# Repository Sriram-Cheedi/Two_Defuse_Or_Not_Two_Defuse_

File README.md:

# Two Defuse or Not Two Defuse
> **Created by The Barbies** | COMS30043 2025 Team Project

This project aims to create an innovative and tense cooperative experience for players by utilising custom hardware. 

The application runs on an asymmetric two-input system: one player operates within the Unity game world created for the project, while the other operates a custom physical hardware controller to communicate and defuse the bomb.

Technical report on the project can be found [here](./docs/Report_Redacted.pdf) (May require downloading due to file size).

Watch the technical video and trailer [here](https://www.youtube.com/watch?v=A18D9NIgztE).

---

## Project Setup

To fully experience this project, a physical 'hardware bomb' controller is required.

### Prerequisites
*   **Microcontroller:** Teensy 4.1
*   **IDE:** Visual Studio Code with the [PlatformIO extension](https://platformio.org/)
*   **Game Engine:** Unity 6.3 LTS

### 1. Hardware Setup
1. Clone this git repository to your local machine.
2. Open the `Hardware/ControllerV0.1` folder in Visual Studio Code.
3. Ensure the **PlatformIO** extension is installed and active.
4. Plug the Teensy 4.1 microcontroller into your PC via USB.
5. Press the PlatformIO **Upload** button (the right-pointing arrow in the bottom status bar) and wait for the upload to finish.

### 2. Software (Unity) Setup
1. Open the `Team_Project` folder in the Unity Editor and import any required packages.
2. Build the project using **Build Profiles**, selecting your target operating system.
3. Connect the flashed hardware controller to any open serial USB port on your device.
4. Launch the built executable.
5. Enjoy and try not to explode!

> **Note:** If you do not have the required custom hardware, the level will still open and assign a Mock API. However, the game will **not be playable**, as the physical interactions required to navigate and access the game states will be absent.

---

## Project Structure

```text
├── Games Project Pitch Design Documents.pdf
├── Hardware
│   ├── Circuit_Designs
│   ├── ControllerV0.1
│   ├── Example Code
│   └── Manufacturing Drawings
├── Hardware-Software_Interaction.md
├── README.md
├── Team_Project  (Unity Project Root)
│   ├── Assets
│   ├── Packages
│   ├── ProjectSettings
│   └── ... (Builds and project files)
└── The Barbies - Team Project Pitches.pdf

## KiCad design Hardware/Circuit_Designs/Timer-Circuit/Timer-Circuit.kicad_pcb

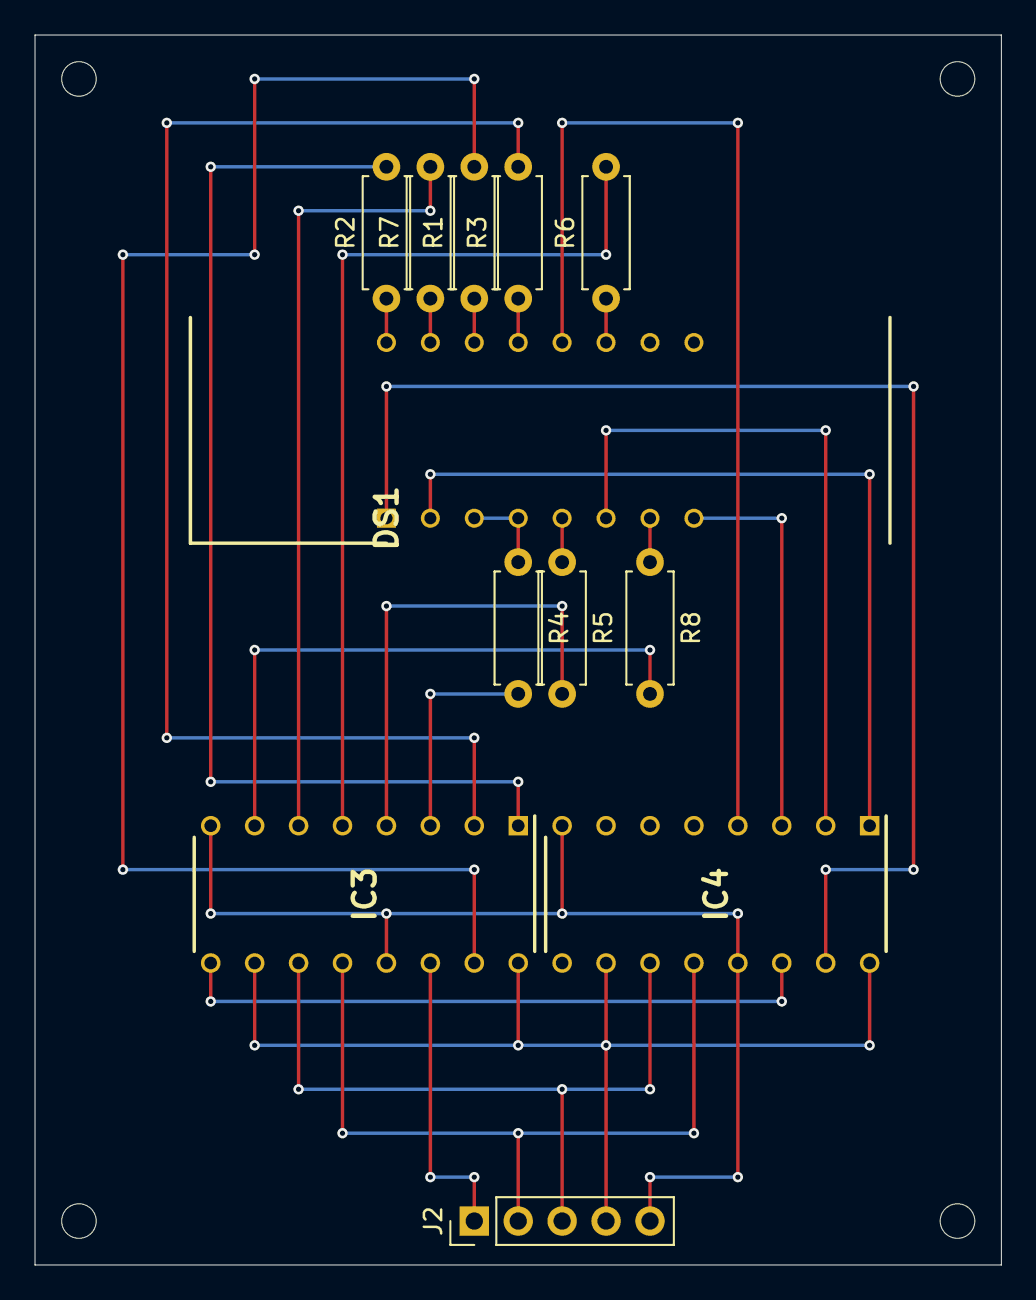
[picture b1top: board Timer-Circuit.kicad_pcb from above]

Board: 2 copper layers, 55.9 x 71.1 mm, 12 parts (0 on the bottom side), 27 nets.

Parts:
DS1: TDCR1060M; DIPS1016W50P254L4020H725Q16N
IC3, IC4: SN74HC595NE4; DIP794W53P254L1930H508Q16N
J2: Conn_01x05; PinHeader_1x05_P2.54mm_Vertical
R1, R2, R3, R4, R5, R6, R7, R8: R_Small; R_Axial_DIN0207_L6.3mm_D2.5mm_P7.62mm_Horizontal

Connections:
unnamed: DS1.14 (ANODE_A), R1.1
unnamed: DS1.16 (ANODE_B), R2.1
unnamed: DS1.13 (ANODE_C), R3.1
unnamed: DS1.3 (ANODE_D), DS1.4 (COMMON_CATHODE_L1_L2), R4.1
unnamed: DS1.7 (ANODE_DP), R8.1
unnamed: DS1.5 (ANODE_E), R5.1
unnamed: DS1.11 (ANODE_F), R6.1
unnamed: DS1.15 (ANODE_G), R7.1
unnamed: DS1.12 (ANODE_L1L2), IC4.4 (QE)
unnamed: DS1.1 (COMMON_CATHODE_D1), IC4.15 (QA)
unnamed: DS1.2 (COMMON_CATHODE_D2), IC4.1 (QB)
unnamed: DS1.6 (COMMON_CATHODE_D3), IC4.2 (QC)
unnamed: DS1.8 (COMMON_CATHODE_D4), IC4.3 (QD)
unnamed: IC3.8 (GND), IC3.13 (~OE), IC4.8 (GND), IC4.13 (~OE), J2.5
unnamed: IC3.15 (QA), R1.2
unnamed: IC3.1 (QB), R2.2
unnamed: IC3.2 (QC), R3.2
unnamed: IC3.3 (QD), R4.2
unnamed: IC3.4 (QE), R5.2
unnamed: IC3.5 (QF), R6.2
unnamed: IC3.6 (QG), R7.2
unnamed: IC3.9 (QH'), IC4.14 (SER)
unnamed: IC3.7 (QH), R8.2
unnamed: IC3.12 (RCLK), IC4.12 (RCLK), J2.2
unnamed: IC3.14 (SER), J2.1
unnamed: IC3.11 (SRCLK), IC4.11 (SRCLK), J2.3
unnamed: IC3.10 (~SRCLR), IC3.16 (VCC), IC4.10 (~SRCLR), IC4.16 (VCC), J2.4

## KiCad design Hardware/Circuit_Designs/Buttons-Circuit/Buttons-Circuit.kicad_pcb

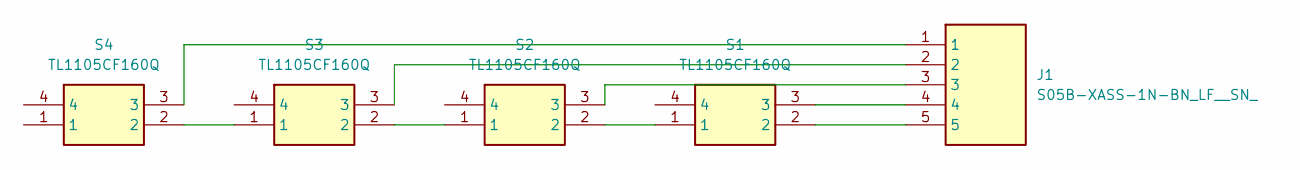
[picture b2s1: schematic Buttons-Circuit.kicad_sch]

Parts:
J1: S05B-XASS-1N-BN_LF__SN_; S05BXASS1NBNLFSN; Manufacturer_Part_Number S05B-XASS-1N-BN(LF)(SN); Mouser Part Number 306-S05BXASS1NBNLFSN
S1, S2, S3, S4: TL1105CF160Q; Manufacturer_Part_Number TL1105CF160Q; Mouser Part Number 612-TL1105C

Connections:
unnamed: J1.1, S4.3
unnamed: J1.2, S3.3
unnamed: J1.3, S2.3
unnamed: J1.4, S1.3
unnamed: J1.5, S1.2
unnamed: S1.1, S2.2
unnamed: S2.1, S3.2
unnamed: S3.1, S4.2

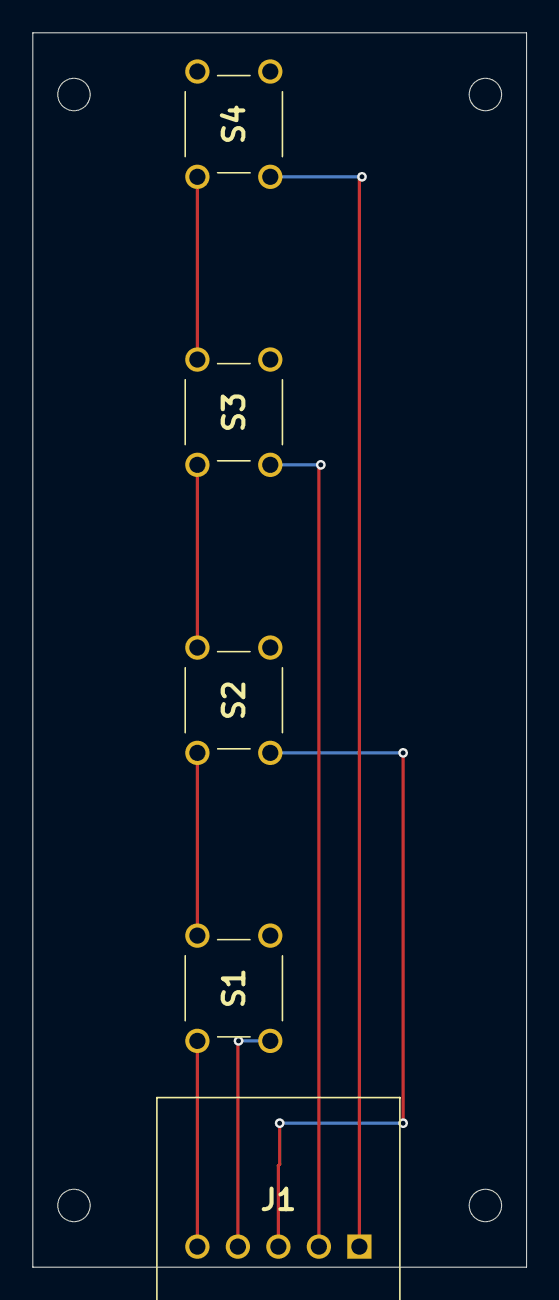
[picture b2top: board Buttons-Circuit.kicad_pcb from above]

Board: 2 copper layers, 30.5 x 76.2 mm, 5 parts (0 on the bottom side), 8 nets.

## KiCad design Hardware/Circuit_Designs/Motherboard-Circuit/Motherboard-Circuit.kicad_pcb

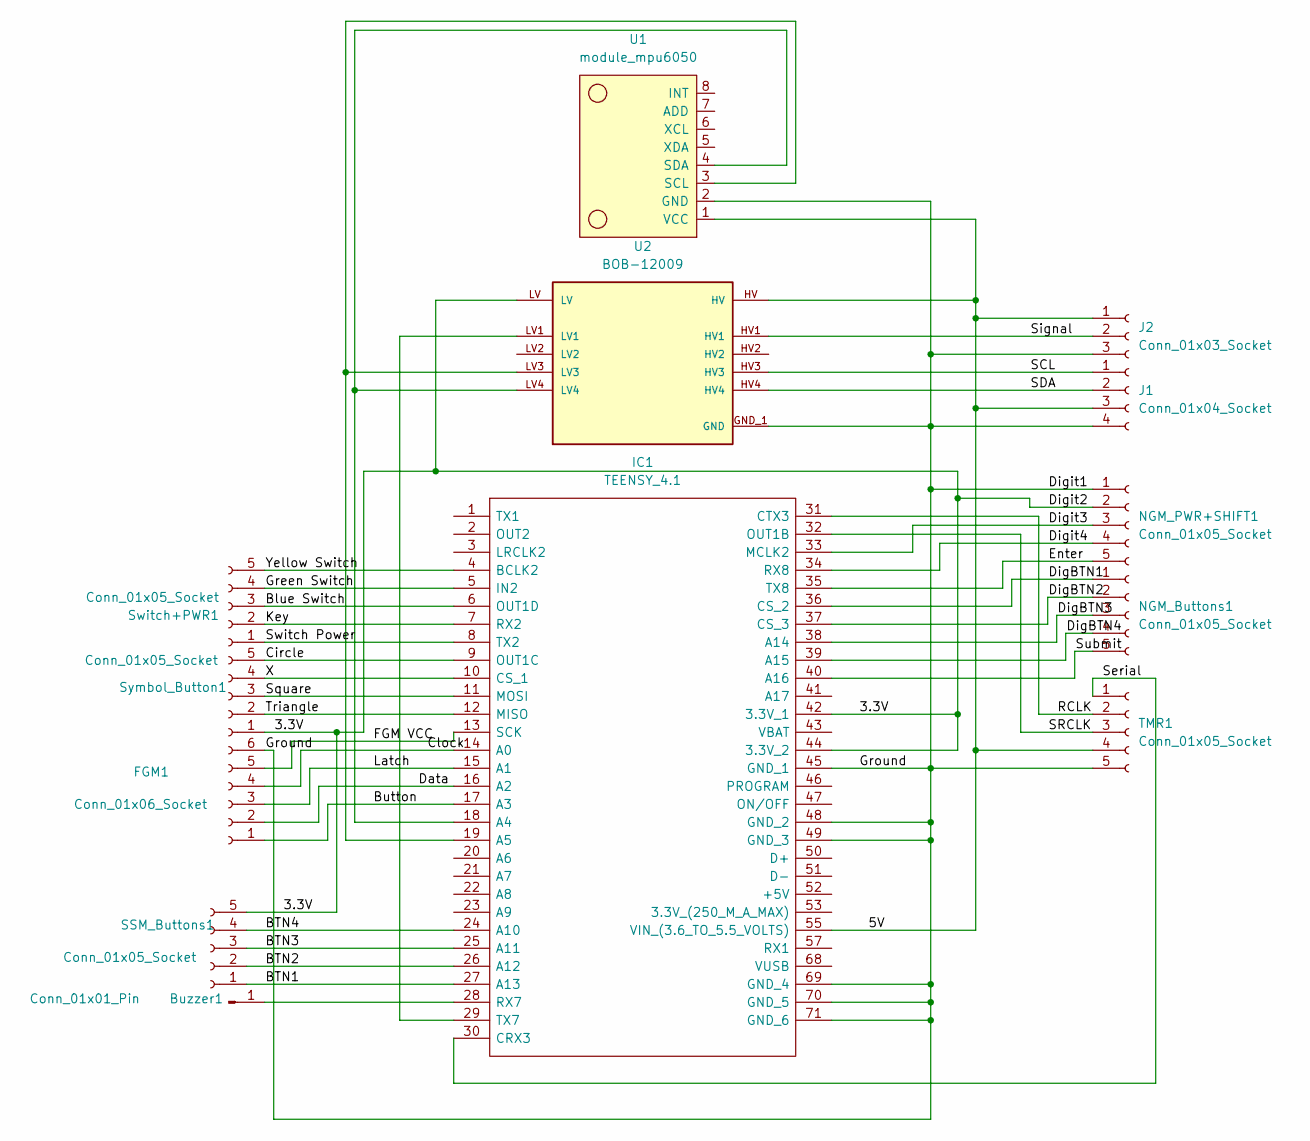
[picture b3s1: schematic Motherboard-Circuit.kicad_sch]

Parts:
Buzzer1: Conn_01x01_Pin; PinHeader_1x01_P2.54mm_Vertical
FGM1: Conn_01x06_Socket; Molex_KK-254_AE-6410-06A_1x06_P2.54mm_Vertical
IC1: TEENSY_4.1; TEENSY41; Manufacturer_Part_Number TEENSY 4.1
J1: Conn_01x04_Socket; Molex_KK-254_AE-6410-04A_1x04_P2.54mm_Vertical
J2: Conn_01x03_Socket; Molex_KK-254_AE-6410-03A_1x03_P2.54mm_Vertical
NGM_Buttons1: Conn_01x05_Socket; Molex_KK-254_AE-6410-05A_1x05_P2.54mm_Vertical
NGM_PWR+SHIFT1: Conn_01x05_Socket; Molex_KK-254_AE-6410-05A_1x05_P2.54mm_Vertical
SSM_Buttons1: Conn_01x05_Socket; Molex_KK-254_AE-6410-05A_1x05_P2.54mm_Vertical
Switch+PWR1: Conn_01x05_Socket; Molex_KK-254_AE-6410-05A_1x05_P2.54mm_Vertical
Symbol_Button1: Conn_01x05_Socket; Molex_KK-254_AE-6410-05A_1x05_P2.54mm_Vertical
TMR1: Conn_01x05_Socket; Molex_KK-254_AE-6410-05A_1x05_P2.54mm_Vertical
U1: module_mpu6050
U2: BOB-12009; CONV_BOB-12009; PARTREV 01

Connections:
/3.3V: IC1.42 (3.3V_1), IC1.44 (3.3V_2), NGM_PWR+SHIFT1.2, SSM_Buttons1.5, Symbol_Button1.1, U2.LV
/5V: IC1.55 (VIN_(3.6_TO_5.5_VOLTS)), J1.3, J2.1, TMR1.4, U1.1 (VCC), U2.HV
/BTN1: IC1.27 (A13), SSM_Buttons1.1
/BTN2: IC1.26 (A12), SSM_Buttons1.2
/BTN3: IC1.25 (A11), SSM_Buttons1.3
/BTN4: IC1.24 (A10), SSM_Buttons1.4
/Blue Switch: IC1.6 (OUT1D), Switch+PWR1.3
/Button: FGM1.1, IC1.17 (A3)
/Circle: IC1.9 (OUT1C), Symbol_Button1.5
/Clock: FGM1.4, IC1.14 (A0)
/Clock_Pin: IC1.35 (TX8), NGM_PWR+SHIFT1.5
/DS_Pin: IC1.33 (MCLK2), NGM_PWR+SHIFT1.3
/Data: FGM1.2, IC1.16 (A2)
/DigBTN1: IC1.36 (CS_2), NGM_Buttons1.1
/DigBTN2: IC1.37 (CS_3), NGM_Buttons1.2
/DigBTN3: IC1.38 (A14), NGM_Buttons1.3
/DigBTN4: IC1.39 (A15), NGM_Buttons1.4
/FGM VCC: FGM1.5, IC1.13 (SCK)
/Green Switch: IC1.5 (IN2), Switch+PWR1.4
/Key: IC1.7 (RX2), Switch+PWR1.2
/Latch: FGM1.3, IC1.15 (A1)
/Latch Pin: IC1.34 (RX8), NGM_PWR+SHIFT1.4
/RCLK: IC1.31 (CTX3), TMR1.2
/SCL: J1.1, U2.HV3
/SDA: J1.2, U2.HV4
/SRCLK: IC1.32 (OUT1B), TMR1.3
/Serial: IC1.30 (CRX3), TMR1.1
/Signal: J2.2, U2.HV1
/Square: IC1.11 (MOSI), Symbol_Button1.3
/Submit: IC1.40 (A16), NGM_Buttons1.5
/Triangle: IC1.12 (MISO), Symbol_Button1.2
/X: IC1.10 (CS_1), Symbol_Button1.4
/Yellow Switch: IC1.4 (BCLK2), Switch+PWR1.5
GND: FGM1.6, IC1.45 (GND_1), IC1.48 (GND_2), IC1.49 (GND_3), IC1.69 (GND_4), IC1.70 (GND_5), IC1.71 (GND_6), J1.4, J2.3, NGM_PWR+SHIFT1.1, TMR1.5, U1.2 (GND), U2.GND_1 (GND), U2.GND_2 (GND)
unnamed: Buzzer1.1, IC1.28 (RX7)
unnamed: IC1.18 (A4), U1.4 (SDA), U2.LV4
unnamed: IC1.19 (A5), U1.3 (SCL), U2.LV3
unnamed: IC1.8 (TX2), Switch+PWR1.1
unnamed: IC1.29 (TX7), U2.LV1

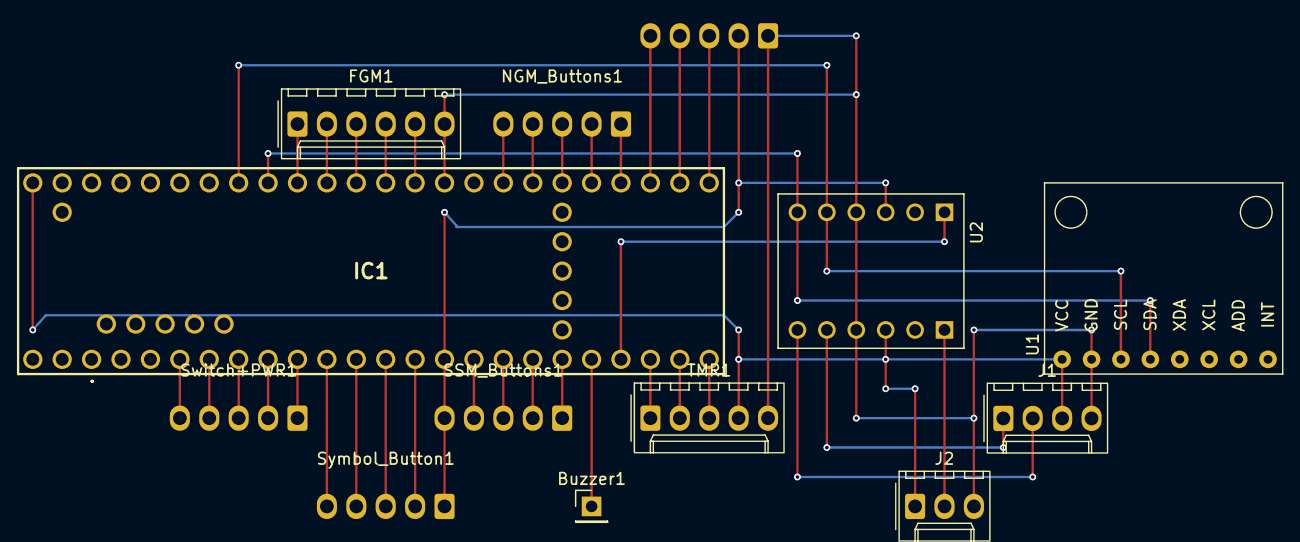
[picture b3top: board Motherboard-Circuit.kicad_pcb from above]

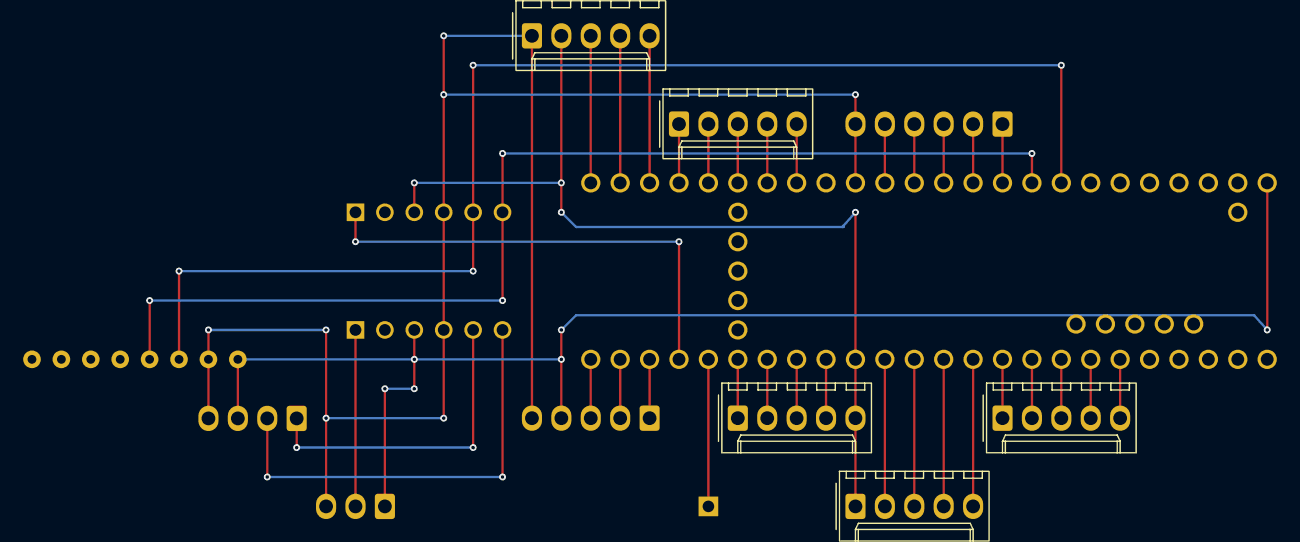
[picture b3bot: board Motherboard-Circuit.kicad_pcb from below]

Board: 2 copper layers, 13 parts (5 on the bottom side), 39 nets.

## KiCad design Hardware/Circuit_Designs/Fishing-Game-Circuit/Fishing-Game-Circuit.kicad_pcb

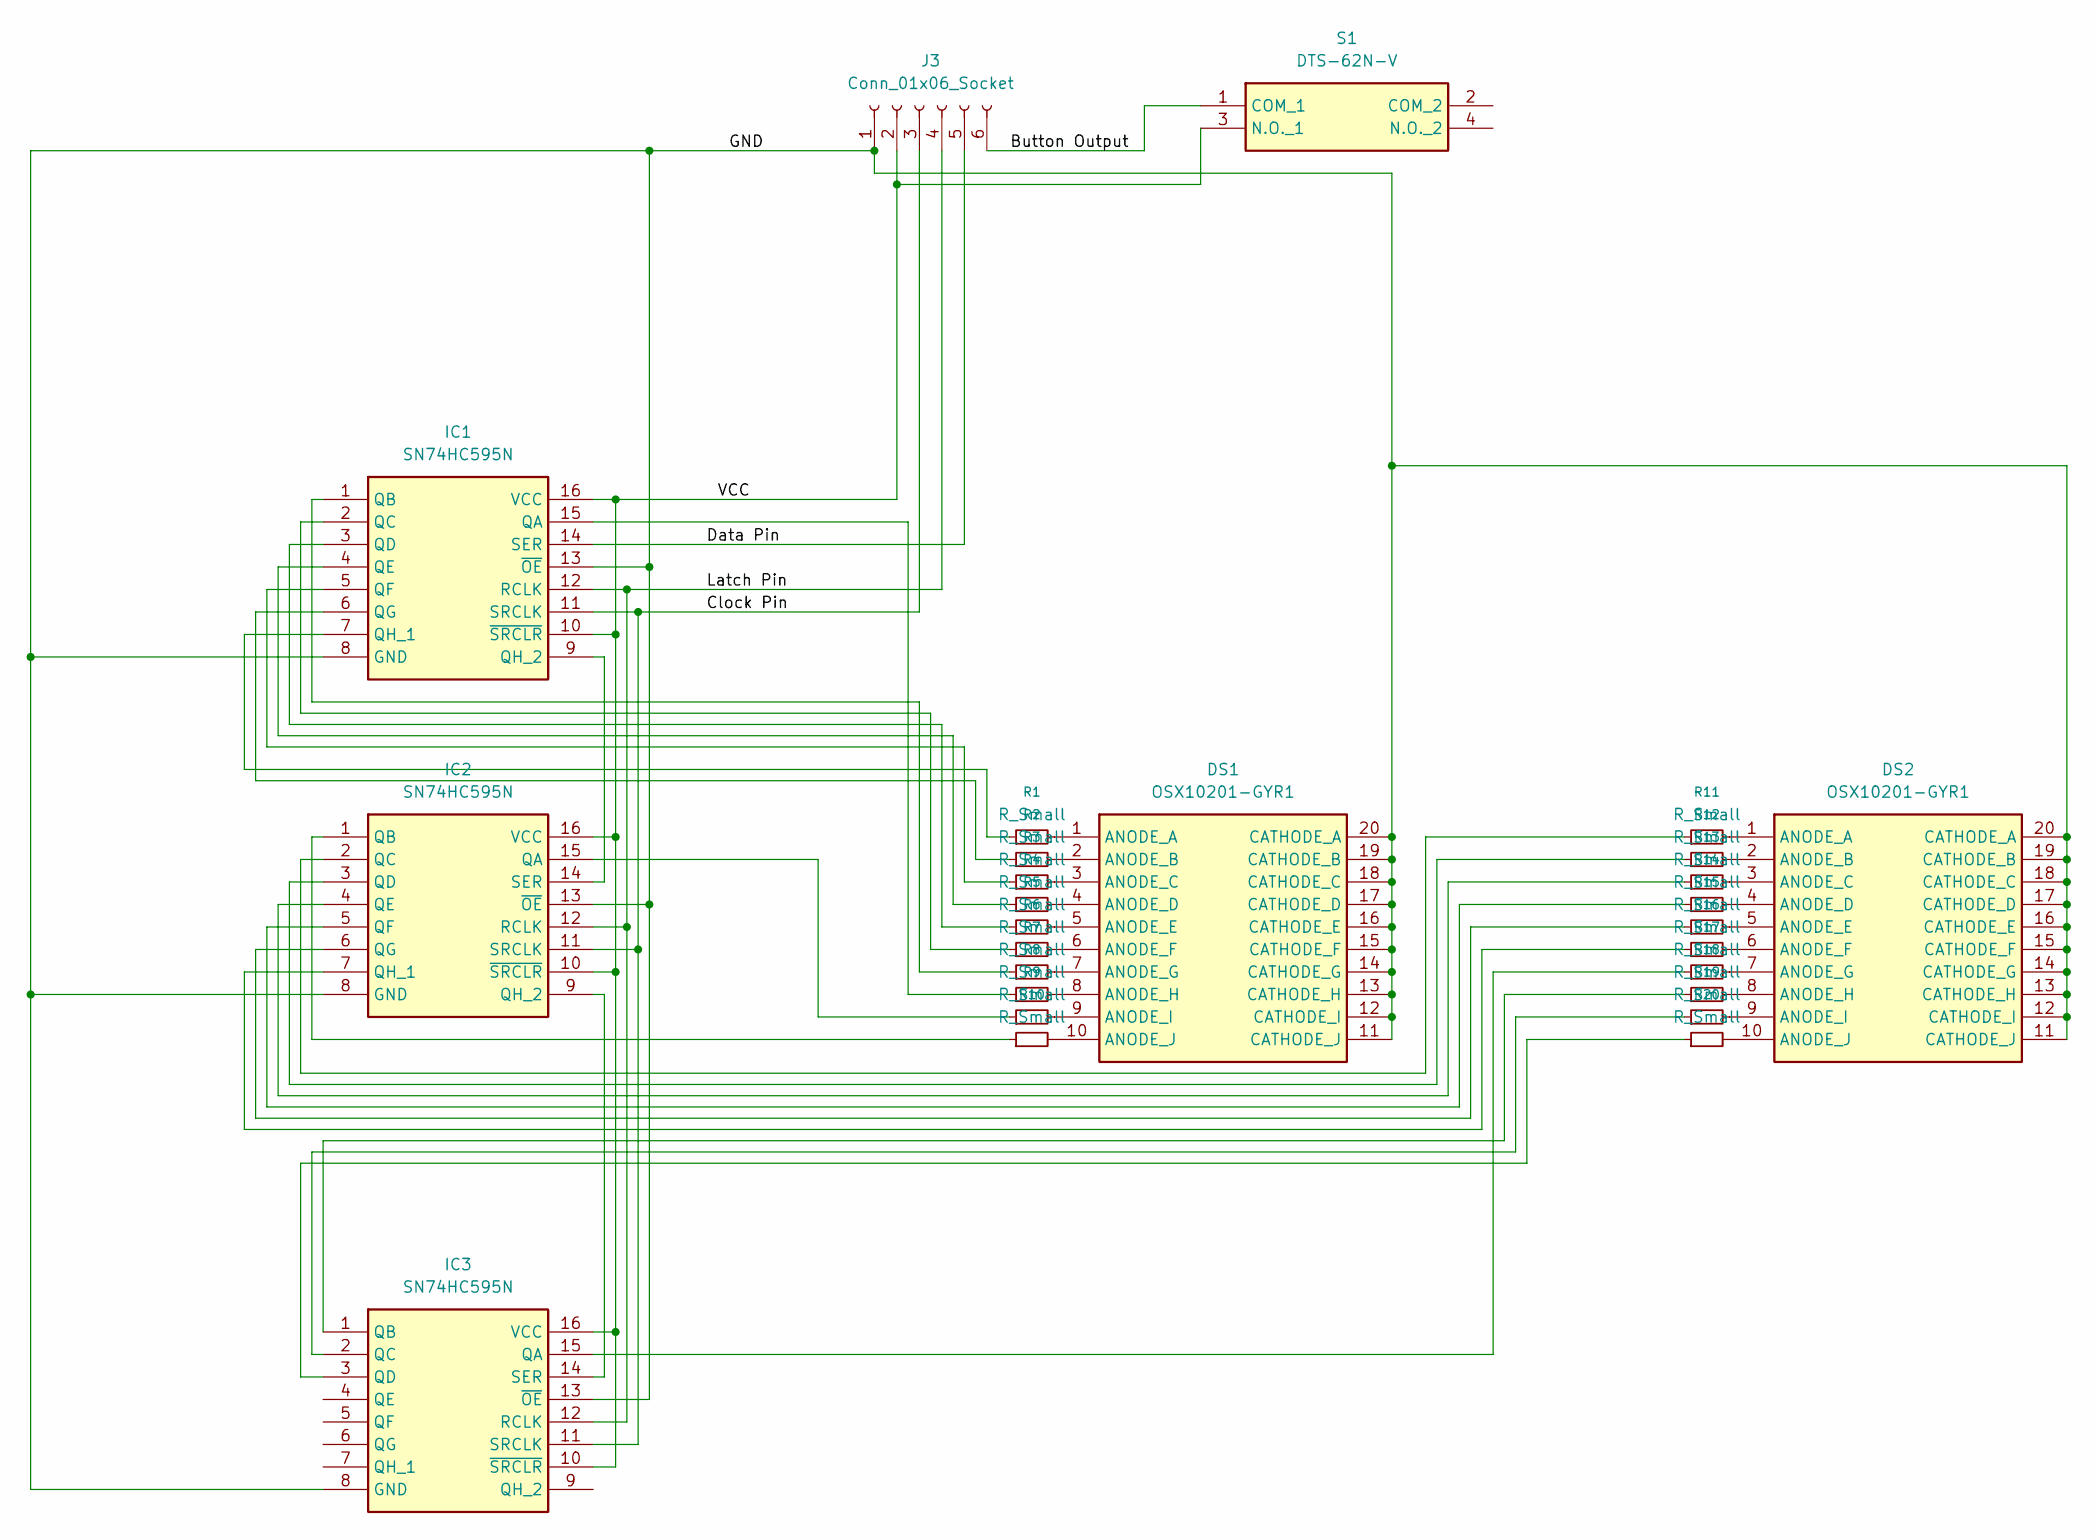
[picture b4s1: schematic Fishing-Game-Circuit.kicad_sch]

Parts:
DS1, DS2: OSX10201-GYR1; DIPS760W45P254L2550H815Q20N; Manufacturer_Part_Number OSX10201-GYR1
IC1, IC2, IC3: SN74HC595N; DIP794W53P254L1930H508Q16N; Manufacturer_Part_Number SN74HC595N; Mouser Part Number 595-SN74HC595N
J3: Conn_01x06_Socket; Molex_SL_171971-0006_1x06_P2.54mm_Vertical
R1, R2, R3, R4, R5, R6, R7, R8, R9, R10, R11, R12, R13, R14, R15, R16, R17, R18, R19, R20: R_Small; R_Axial_DIN0207_L6.3mm_D2.5mm_P7.62mm_Horizontal
S1: DTS-62N-V; DTS62NV; Manufacturer_Part_Number DTS-62N-V; Mouser Part Number 113-DTS-62N-V

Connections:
/Button Output: J3.6, S1.1 (COM_1)
/Clock Pin: IC1.11 (SRCLK), IC2.11 (SRCLK), IC3.11 (SRCLK), J3.3
/Data Pin: IC1.14 (SER), J3.5
/GND: DS1.11 (CATHODE_J), DS1.12 (CATHODE_I), DS1.13 (CATHODE_H), DS1.14 (CATHODE_G), DS1.15 (CATHODE_F), DS1.16 (CATHODE_E), DS1.17 (CATHODE_D), DS1.18 (CATHODE_C), DS1.19 (CATHODE_B), DS1.20 (CATHODE_A), DS2.11 (CATHODE_J), DS2.12 (CATHODE_I), DS2.13 (CATHODE_H), DS2.14 (CATHODE_G), DS2.15 (CATHODE_F), DS2.16 (CATHODE_E), DS2.17 (CATHODE_D), DS2.18 (CATHODE_C), DS2.19 (CATHODE_B), DS2.20 (CATHODE_A), IC1.8 (GND), IC1.13 (~OE), IC2.8 (GND), IC2.13 (~OE), IC3.8 (GND), IC3.13 (~OE), J3.1
/Latch Pin: IC1.12 (RCLK), IC2.12 (RCLK), IC3.12 (RCLK), J3.4
/VCC: IC1.10 (~SRCLR), IC1.16 (VCC), IC2.10 (~SRCLR), IC2.16 (VCC), IC3.10 (~SRCLR), IC3.16 (VCC), J3.2, S1.3 (N.O._1)
unnamed: DS1.1 (ANODE_A), R1.2
unnamed: DS1.2 (ANODE_B), R2.2
unnamed: DS1.3 (ANODE_C), R3.2
unnamed: DS1.4 (ANODE_D), R4.2
unnamed: DS1.5 (ANODE_E), R5.2
unnamed: DS1.6 (ANODE_F), R6.2
unnamed: DS1.7 (ANODE_G), R7.2
unnamed: DS1.8 (ANODE_H), R8.2
unnamed: DS1.9 (ANODE_I), R9.2
unnamed: DS1.10 (ANODE_J), R10.2
unnamed: DS2.1 (ANODE_A), R11.2
unnamed: DS2.2 (ANODE_B), R12.2
unnamed: DS2.3 (ANODE_C), R13.2
unnamed: DS2.4 (ANODE_D), R14.2
unnamed: DS2.5 (ANODE_E), R15.2
unnamed: DS2.6 (ANODE_F), R16.2
unnamed: DS2.7 (ANODE_G), R17.2
unnamed: DS2.8 (ANODE_H), R18.2
unnamed: DS2.9 (ANODE_I), R19.2
unnamed: DS2.10 (ANODE_J), R20.2
unnamed: IC1.15 (QA), R8.1
unnamed: IC1.1 (QB), R7.1
unnamed: IC1.2 (QC), R6.1
unnamed: IC1.3 (QD), R5.1
unnamed: IC1.4 (QE), R4.1
unnamed: IC1.5 (QF), R3.1
unnamed: IC1.6 (QG), R2.1
unnamed: IC1.7 (QH_1), R1.1
unnamed: IC1.9 (QH_2), IC2.14 (SER)
unnamed: IC2.15 (QA), R9.1
unnamed: IC2.1 (QB), R10.1
unnamed: IC2.2 (QC), R11.1
unnamed: IC2.3 (QD), R12.1
unnamed: IC2.4 (QE), R13.1
unnamed: IC2.5 (QF), R14.1
unnamed: IC2.6 (QG), R15.1
unnamed: IC2.7 (QH_1), R16.1
unnamed: IC2.9 (QH_2), IC3.14 (SER)
unnamed: IC3.15 (QA), R17.1
unnamed: IC3.1 (QB), R18.1
unnamed: IC3.2 (QC), R19.1
unnamed: IC3.3 (QD), R20.1

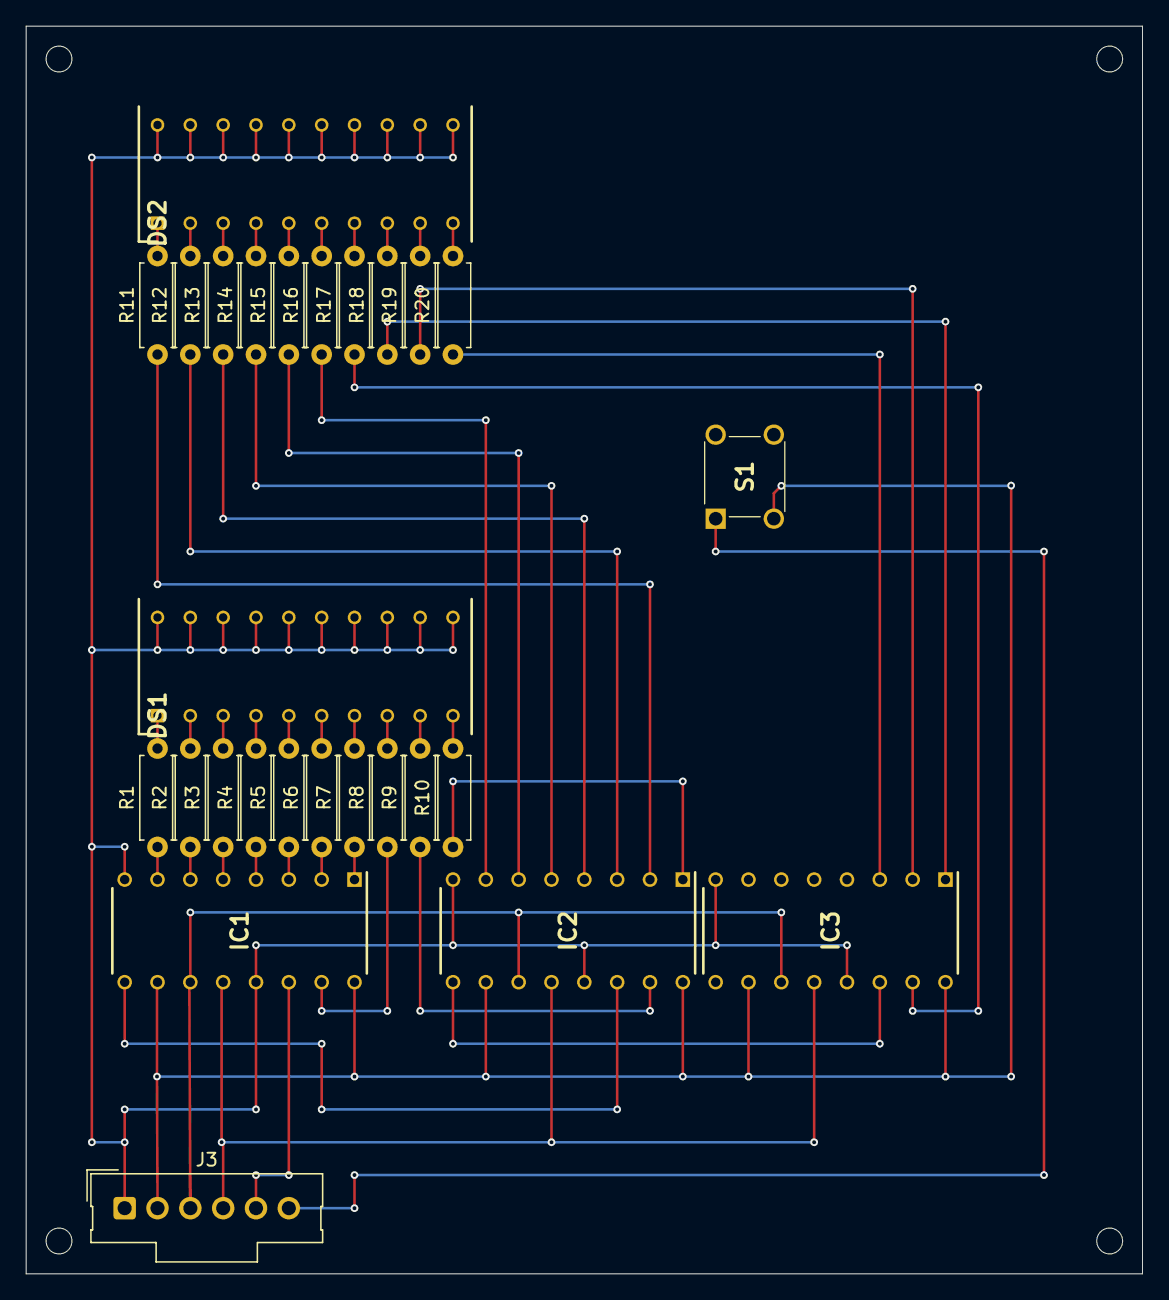
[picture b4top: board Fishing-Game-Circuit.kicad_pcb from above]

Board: 2 copper layers, 86.4 x 96.5 mm, 27 parts (0 on the bottom side), 48 nets.

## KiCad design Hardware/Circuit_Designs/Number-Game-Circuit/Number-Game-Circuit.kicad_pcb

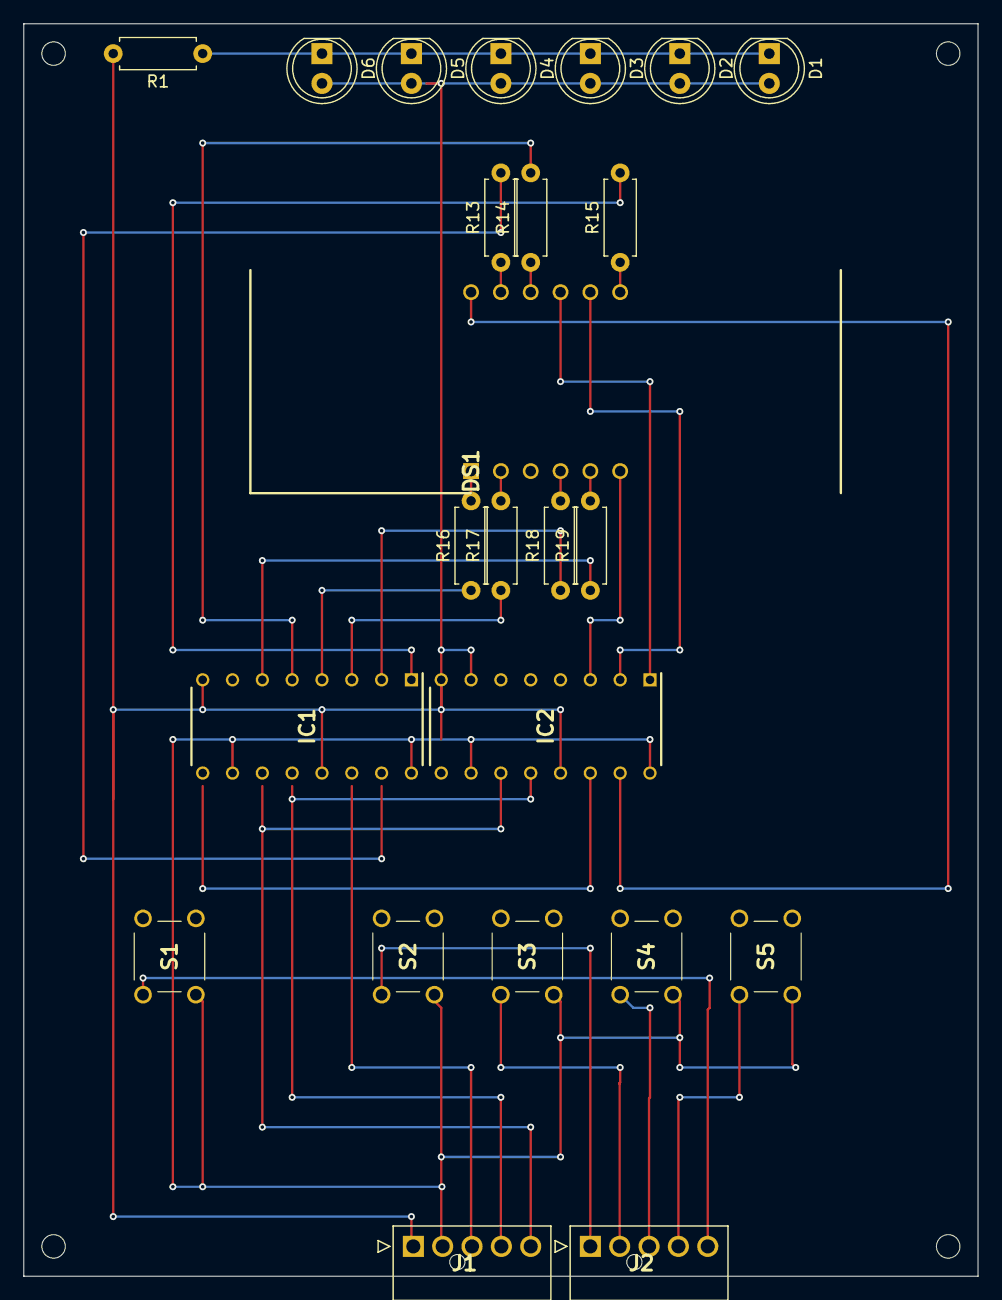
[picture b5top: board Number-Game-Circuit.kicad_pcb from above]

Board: 2 copper layers, 81.3 x 106.7 mm, 24 parts (0 on the bottom side), 30 nets.

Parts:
D1, D2, D3, D4, D5, D6: LED; LED_D5.0mm_Clear
DS1: LDQ-M516RI; DIPS1524W50P254L5030H800Q12N
IC1, IC2: SN74HC595N; DIP794W53P254L1930H508Q16N
J1, J2: 1053091305; 1053091405
R1, R13, R14, R15, R16, R17, R18, R19: R_Small; R_Axial_DIN0207_L6.3mm_D2.5mm_P7.62mm_Horizontal
S1, S2, S3, S4, S5: TL1105CF160Q

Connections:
/Clock PIN: IC1.11 (SRCLK), IC2.11 (SRCLK), J1.5
/DS PIN: IC1.14 (SER), J1.3
/Ground: D1.1 (K), D2.1 (K), D3.1 (K), D4.1 (K), D5.1 (K), D6.1 (K), IC1.8 (GND), IC1.13 (~OE), IC2.8 (GND), IC2.13 (~OE), J1.1, R1.2
/Latch PIN: IC1.12 (RCLK), IC2.12 (RCLK), J1.4
/VCC: IC1.10 (~SRCLR), IC1.16 (VCC), IC2.10 (~SRCLR), IC2.16 (VCC), J1.2, S1.1, S2.3, S3.3, S4.3, S5.3
unnamed: D1.2 (A), D2.2 (A), D3.2 (A), D4.2 (A), D5.2 (A), D6.2 (A), IC2.7 (QH_1)
unnamed: DS1.1, R16.2
unnamed: DS1.2, R17.2
unnamed: DS1.4, R18.2
unnamed: DS1.5, R19.2
unnamed: DS1.7, R15.1
unnamed: DS1.10, R14.1
unnamed: DS1.11, R13.1
unnamed: IC1.15 (QA), R13.2
unnamed: IC1.1 (QB), R15.2
unnamed: IC1.2 (QC), R18.1
unnamed: IC1.3 (QD), R17.1
unnamed: IC1.4 (QE), R16.1
unnamed: IC1.5 (QF), R14.2
unnamed: IC1.6 (QG), R19.1
unnamed: IC1.9 (QH_2), IC2.14 (SER)
unnamed: DS1.12, IC2.15 (QA)
unnamed: DS1.9, IC2.1 (QB)
unnamed: DS1.8, IC2.2 (QC)
unnamed: DS1.6, IC2.3 (QD)
unnamed: J2.1, S2.2
unnamed: J2.2, S3.2
unnamed: J2.3, S4.2
unnamed: J2.4, S5.2
unnamed: J2.5, S1.4

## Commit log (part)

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2026-02-09 fixed sound
2026-02-09 Add Simon Says commands to interaction documentation
    Added commands for Simon Says game including status retrieval and sequence setting.
2026-02-10 added sendSeq function
2026-02-10 added cpp and header file for the fishing game.
2026-02-10 created skeleton for the fishing game header
2026-02-10 fixed build issue
2026-02-10 added intervals for score checking and added a debounce for the button. tweaked other interval times.
2026-02-10 added script stuff
2026-02-10 started circuit diagram for number game. did this one the wrong branch
2026-02-11 started the schematics for the number game
2026-02-12 Finished schematic for the number game.
2026-02-12 Updated API
2026-02-12 made schematic shorter
2026-02-12 SSM Almost working, crashing on reset.
2026-02-12 fixed JST XH pin placement
2026-02-12 moved a cut to be above pins
2026-02-12 added assets creator
2026-02-12 update assets creator code
2026-02-12 Added serial pings when SSM state is changed
2026-02-12 Formatting Dependancies
2026-02-12 Removing Comments in main
2026-02-13 added sounds for end scene
2026-02-13 added interactible keypad
2026-02-13 Remove Neopixel Library
2026-02-13 Made State, Status(), buttonPressed thread safe. Status() is now called from update function on main thread.
2026-02-13 SSM .h comments
2026-02-14 Added delay after fail flashes, .h comments
2026-02-16 minor changes to the number game schematic.
2026-02-16 started working on the set and status function for number and fishing game
2026-02-16 Changed main for SSM test
2026-02-16 fixed interaction testing lvl
2026-02-16 Revert StartLevel scene
2026-02-16 Added Complete sequence on game completion
2026-02-16 Modify cache key in testing workflow
    Updated cache key for Library to include Team_Project path.
2026-02-16 fixed systems prefab
2026-02-16 Removed puzzle maanger from systems as this should be inited from the scene in which puzzels reside not globally
2026-02-16 Update GitHub Actions workflow for caching and LFS
2026-02-17 End game animation
2026-02-17 fixed
2026-02-17 Decorated the level
2026-02-17 added player observer
2026-02-17 Added small delay to main loop for thread safety
2026-02-17 fishing game uses button class.
2026-02-17 Update SSM button pins
2026-02-18 MVP fixed
2026-02-18 mvp build
2026-02-18 Changed SSM timing, main now sets SSM running
2026-02-18 decoupled rigidmovement into multiple components
2026-02-20 added state machines and fixed jump
2026-02-21 updates serial code
2026-02-21 Made the game to pause if hardware disconnects
2026-02-21 added states for metal and plastic
2026-02-21 fixed bugs and added strategy for movement
2026-02-22 module registry
2026-02-23 added surface types
2026-02-23 Revert "Improve serial communication"
2026-02-25 number game done
2026-02-26 fixed jump added apex hang
2026-02-26 saved
2026-02-26 Change testing runner to Ubuntu 22.04 and add diagnostics
    Updated the testing workflow to use Ubuntu 22.04 and added diagnostics on failure.
2026-02-26 Change runner to Ubuntu 22.04 and improve error handling
    Updated the workflow to use Ubuntu 22.04 and added error handling for docker commands.
2026-02-28 fixed change in air
2026-03-01 prototype for tutorial level
2026-03-01 added basic tutorial card simulation to the gameplay(Will be updated with better logic)
2026-03-01 gyro half fixed
2026-03-01 huds progression
2026-03-01 saved scene
2026-03-02 Fixed template scene | removed old prefabs | added PuzzleManager | Added ConditionalDoors
2026-03-02 removed bloat
2026-03-02 modified NG circuit for new game layout. Designed circuit for Fishing Game
2026-03-02 Update Simon Says status description
2026-03-02 Update testing workflow to only target Unity Currently
2026-03-02 Fixed Simon
2026-03-02 Delete Hardware/SSMCoverPlate.dxf
    File not needed
2026-03-02 SSM_Test file deleted
2026-03-02 changed the connector type on the fishing game
2026-03-02 gravity half fixed
2026-03-02 added conditional door | SSM game | button_interaction
2026-03-02 latest
2026-03-02 Add coverageOptions and customParameters to testing.yml
2026-03-03 added levels
2026-03-03 tutorial cards
2026-03-03 added alert for path choice
2026-03-03 Changed SSM colours
2026-03-03 Save
2026-03-03 unity will now handle number game set. buttons now send status commands
2026-03-03 Changed NGM pins
2026-03-03 massive restructuring of puzzles - not completed but need to test hardware
2026-03-03 Bug fixing
2026-03-03 Update testing.yml to remove push trigger
    Removed push event trigger for main branch.
2026-03-03 cleaned up deprecated functions
2026-03-04 testathon ready
2026-03-04 NGM can be reset
2026-03-04 Fixing puzzle stuff
2026-03-05 restored number game from backup
2026-03-05 made wire between 2 anchors
2026-03-05 updated very first section - not finished
2026-03-05 Blinking Led on NGM set command
2026-03-05 Schematic update
2026-03-06 Added off/on/reset functionality
2026-03-06 Changing disable shiftout
2026-03-06 Disable sets state to 0
2026-03-06 added fence pack | created prefabs | continuing making tutorial section
2026-03-06 Removed Disabled Bool, replaced with state == 0
2026-03-06 SSM State Control Fully implemented
2026-03-06 Off cannot be restored by enable
2026-03-06 crazy duplicates
2026-03-06 changed vfx
2026-03-07 update api for fishing game
2026-03-07 powerToggle function added
2026-03-07 Made update part of component class
2026-03-09 added smoke effect
2026-03-09 smoker init
2026-03-09 half added NGM-Wires
2026-03-10 All modules enable/disable
2026-03-10 fishing game is now constant and send off state every state change
2026-03-10 Working Power on/off and power cycle
2026-03-10 added footsteps sys
2026-03-10 added structre for minor_interactions | added lazer disable
2026-03-11 Adding minor door trigger | Reordering init for Managers / API Objects
2026-03-11 added pre-Beta build
2026-03-11 Working Power Cycle Minigame
2026-03-11 Added automatic checking for hardware connection - defaults to mock if real selected but no hardware found
2026-03-11 LCD restore text after power cycle
2026-03-11 SSM Thread Starting on complete called
2026-03-11 made puzzlemanager start async to wait for API_Provider
2026-03-11 fixed fishing game encoding
2026-03-11 bug fixes
2026-03-11 added player death animation
2026-03-12 Added assets and textures
2026-03-12 fishing game now updated in main
2026-03-12 created smoke
2026-03-12 saved data
2026-03-13 fishing module complete
2026-03-13 added ceiling death
2026-03-13 smoker completed
2026-03-13 All Components Scrambled on power game. Power on flashing.
2026-03-13 LCD Module not overwriting scramble warning. Added complete off serial controll
2026-03-13 Removed Commented section
2026-03-14 finished maze prototype and barred door prototype - no animaations yet
2026-03-14 added player collision
2026-03-15 added UI for mockharware - Half compelted
2026-03-15 made smoker to smoke only in the room the player is
2026-03-15 smoker effect - completed
2026-03-16 smoke added for fourth room
2026-03-16 fixed bars across door logic and init logic for bomb state
2026-03-16 Add assets
2026-03-16 fixed NGM activation point
2026-03-16 NGM if newState == state do nothing
2026-03-16 changed smoker-code
2026-03-16 updated huds
2026-03-17 changed ssm back to random
2026-03-17 Add commands for fishing game, LCD, button, and power
2026-03-17 changed for disable
2026-03-17 fixed bugs
2026-03-17 symbols added
2026-03-17 Increased FGM timer
2026-03-17 Start delay on correct state
2026-03-17 random state is between 0 and 7 now
2026-03-17 reverted to the refactoring version and kept the stable version
2026-03-17 dregged player
2026-03-17 Functional bar door
2026-03-17 Move bars to one side
2026-03-17 changed animation behaviour
2026-03-18 beta ready
2026-03-19 Added Button Circuit Diagram, Added Perminant Disable/Enable, Reset LCD on game start. Fixed SSM debug reporting
2026-03-19 Done!
2026-03-19 started motherboard circuit design
2026-03-19 refactored maze
2026-03-20 added beta build
2026-03-20 firebase backend stuff
2026-03-20 compile error
2026-03-20 Remove tone command from main
2026-03-20 Buttons Circuit final
2026-03-20 All circuit designs have mounting holes
2026-03-20 added spark to maze
2026-03-20 Added text list
2026-03-20 added spark to maze on matscene
2026-03-20 created placeholder leaderboard on mainMenu
2026-03-21 Refactored Puzzle Script Architecture to allow for static access across scenes | Added Score Manager to track and save scores at end of game
2026-03-21 cleanup
2026-03-21 ANON Auth
2026-03-22 made wire cutting better
2026-03-22 Updated FGM Circuit with mounting holes
2026-03-22 added wire cutting logic
2026-03-23 fixed weird assets | added first/last room
2026-03-23 Added mesh asset and door
2026-03-23 added sync logic - finished first/last room
2026-03-23 fixed half collision bugs
2026-03-24 fixed wire jittering
2026-03-24 added wiremapping instructions to the scene
2026-03-24 fixed spinning door and added door opening audio
2026-03-24 Better LCD api done
2026-03-24 dragged player
2026-03-25 Better LCD Done
2026-03-29 Changed NGM Button Footprint
2026-03-29 Fixerd FGM Edge Cuts
2026-03-31 Added Manufacturing Drawings
2026-04-01 closed the door behind the players
2026-04-05 added fov manager to widen fov
2026-04-07 Finished Motherboard circuit
2026-04-08 Gcode Files -- Updated Bomb Skirt Design
2026-04-08 Changed SSM pinout. Added wire cutting
2026-04-08 Lighting Changes
2026-04-09 minor changes to circuit board
2026-04-09 Added buzzer to LCD and FGM
2026-04-09 Flipped Plates
2026-04-09 Fixed tube
2026-04-09 Fixed FGM Siren
2026-04-09 cooperative wire cutting implemented
2026-04-10 Decorate scene day 2
2026-04-10 Button Caps
2026-04-10 bug test
2026-04-10 added sounds and fixed a lot of bugs
2026-04-11 replaced maze tiles with cpus
2026-04-13 added soundtrack for scenes randomized paths for maze add replay
2026-04-14 Stop LCD text flashing on startup, stops corruption
2026-04-14 fixed maze sent
2026-04-14 Added LeaderBoard
2026-04-14 Debouncing for buttons/wirecutting/switches added
2026-04-14 fixed bugs that are blocking gameplay in build version
2026-04-15 Updated Covers Gcode
2026-04-15 Debounce Working
2026-04-15 removed unused jumper wire
2026-04-16 fixed huds in build
2026-04-16 testathon ready with leaderboard
2026-04-16 Final Changes
2026-04-18 frixed all biugs
2026-04-18 build for defuse station2
2026-04-18 added half emoji system
2026-04-18 edited scene
2026-04-19 edited HUDs and gravity system
2026-04-20 Update power status command responses
2026-04-20 added wires to the room
2026-04-20 Removed some legacy files | Added Unit tests for GridManager, PlayerController, Database API | Coverage : 8.2%
2026-04-21 Fitting LCD Cover
2026-04-21 Button debounce time set on creation
2026-04-21 Update wires
2026-04-21 Fixed FGM button unresponsiveness
2026-04-23 RickRoll on Thread
2026-04-23 addded freeze huds and NGM picture
2026-04-23 Background buzz returns after RR
2026-04-24 Seperate header for note definitions, removed old code from FGM
2026-04-24 Lightstrip class added
2026-04-25 SSM button glitch fixed, lightstrip working win/lose/scramble
2026-04-25 chaned few tips
2026-04-25 added soundtrack =
2026-04-26 added soundtracks
2026-04-26 addded smoke for wire cutting room
2026-04-27 Changed to pagma once
2026-04-29 added reconnection handling
2026-04-29 bomb ready
2026-05-06 slightly edited db api
2026-05-06 setup and launch instructions
    Expanded README with setup instructions for hardware and project launch steps.
2026-05-06 Add new test file
2026-05-11 Revise README for project overview and setup steps
    Updated project description and setup instructions for clarity and detail.
2026-05-11 moved files to docs dir
2026-05-11 Revise technical specs link and Unity version
    Updated the technical specifications link and Unity version in the README.
2026-05-22 Clarify technical report download requirement
    Added note about potential file size for the technical report.
2026-05-22 added trailer
2026-05-22 Update video link and thumbnail in README
2026-05-22 Revise technical video link in README
    Updated the link for the technical video and trailer.
2026-05-22 Fix link formatting for technical report and trailer
